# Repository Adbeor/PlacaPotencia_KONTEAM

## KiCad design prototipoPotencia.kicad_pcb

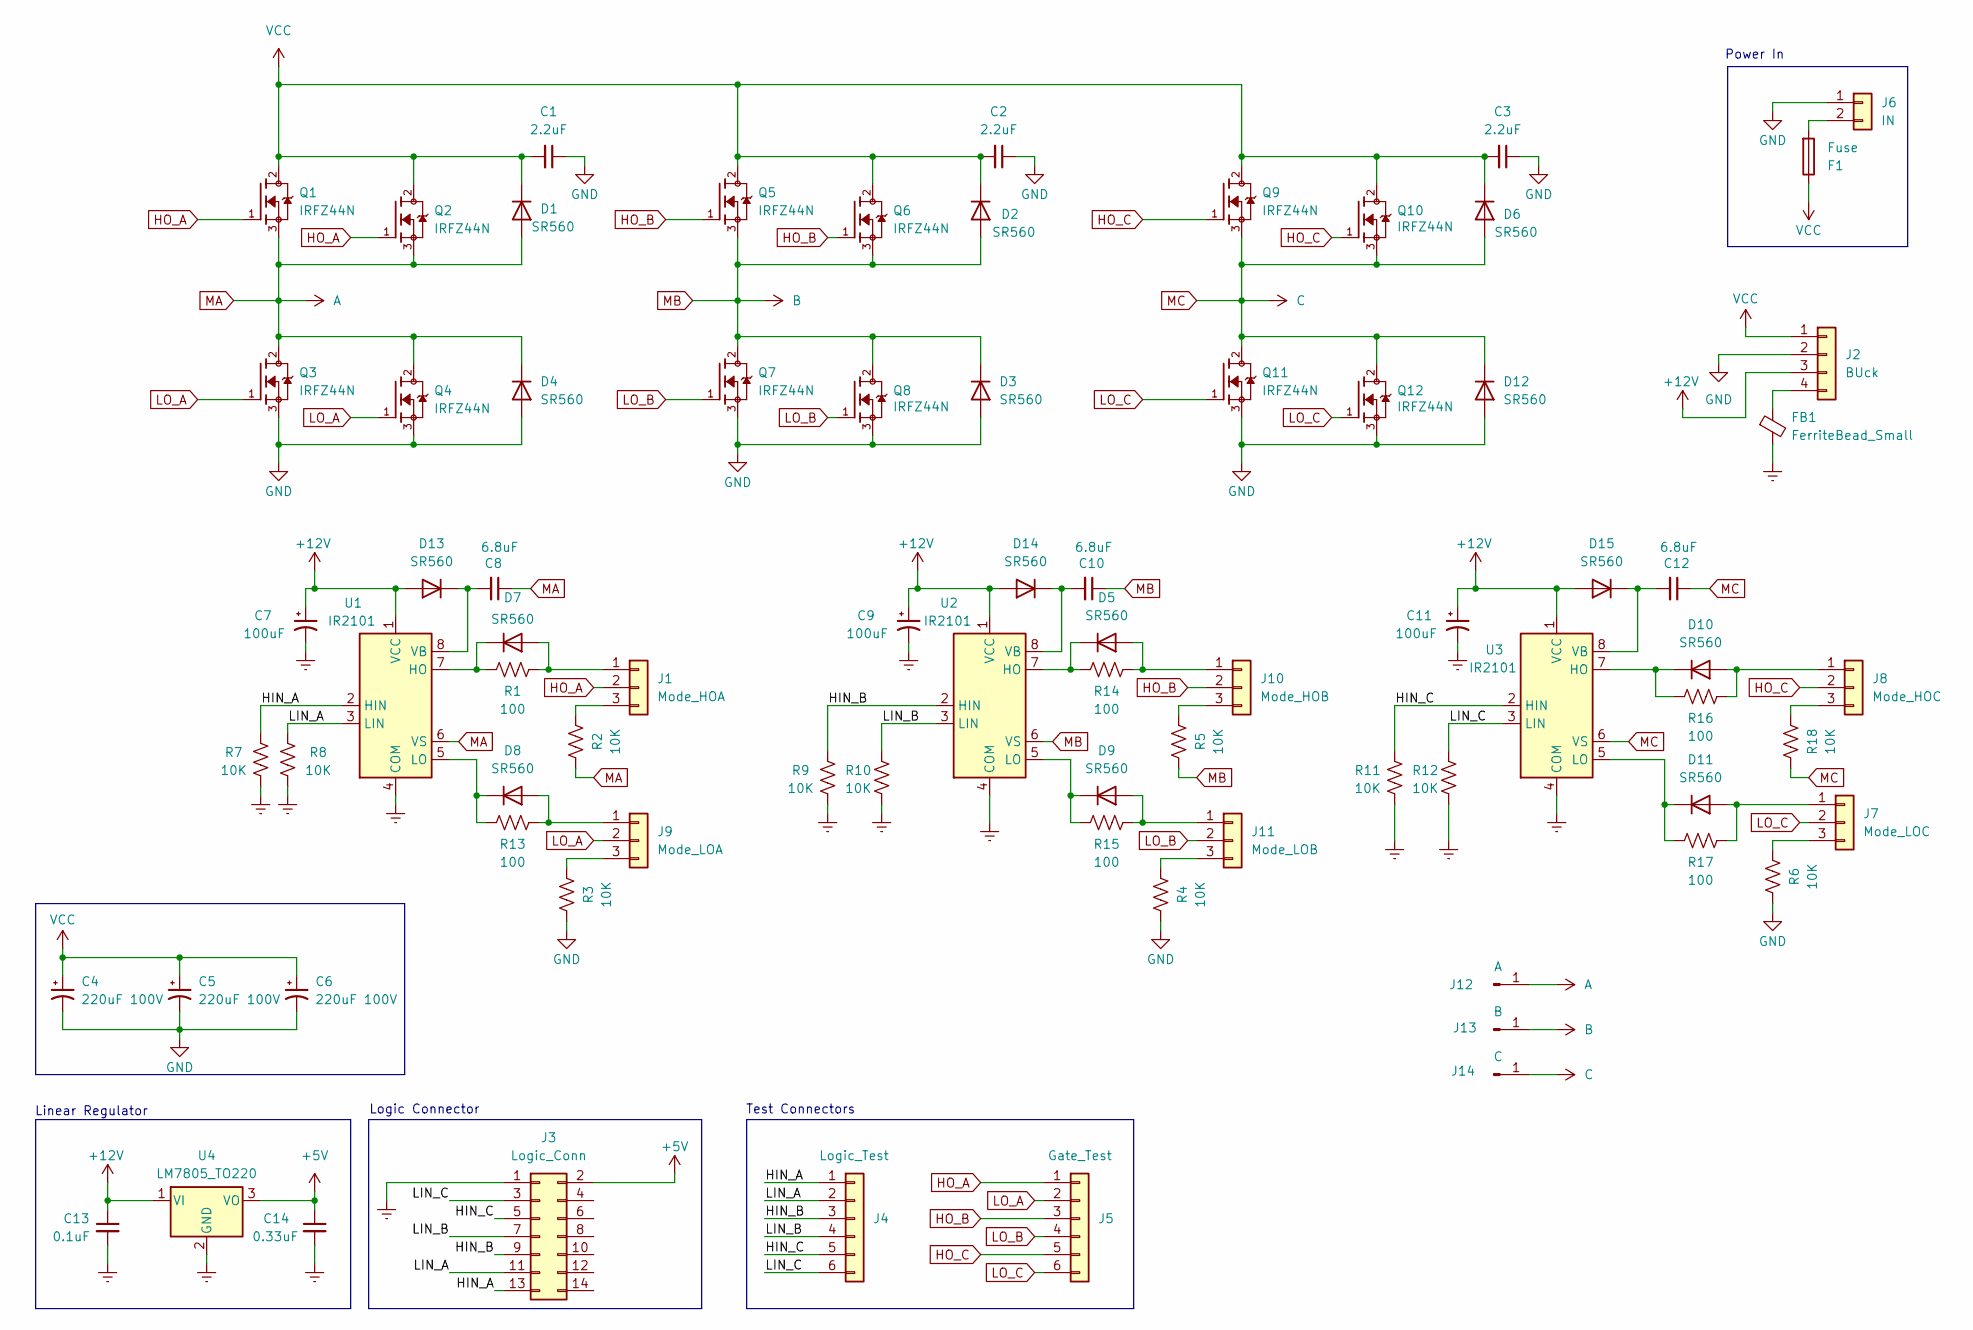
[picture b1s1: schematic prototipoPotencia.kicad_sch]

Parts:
C1, C2, C3: 2.2uF; C_Disc_D5.0mm_W2.5mm_P2.50mm
C4, C5, C6: 220uF 100V; CP_Radial_D10.0mm_P2.50mm
C7, C9, C11: 100uF; C_Radial_D6.3mm_H11.0mm_P2.50mm
C8, C10, C12: 6.8uF; CP_Radial_Tantal_D4.5mm_P2.50mm
C13: 0.1uF; C_Disc_D7.5mm_W2.5mm_P5.00mm
C14: 0.33uF; C_Disc_D7.5mm_W2.5mm_P5.00mm
D1, D2, D3, D4, D5, D6, D7, D8, D9, D10, D11, D12, D13, D14, D15: SR560; D_DO-35_SOD27_P7.62mm_Horizontal
F1: Fuse; Fuse_Littelfuse-LVR100
FB1: FerriteBead_Small; R_Axial_DIN0204_L3.6mm_D1.6mm_P7.62mm_Horizontal
J1: Mode_HOA; PinHeader_1x03_P2.54mm_Vertical
J2: BUck; DC_DC_LM2596_small
J3: Logic_Conn; IDC-Header_2x07_P2.54mm_Vertical
J4: Logic_Test; PinSocket_1x06_P2.54mm_Vertical
J5: Gate_Test; PinSocket_1x06_P2.54mm_Vertical
J6: IN; AMASS_XT60-F_1x02_P7.20mm_Vertical
J7: Mode_LOC; PinHeader_1x03_P2.54mm_Vertical
J8: Mode_HOC; PinHeader_1x03_P2.54mm_Vertical
J9: Mode_LOA; PinHeader_1x03_P2.54mm_Vertical
J10: Mode_HOB; PinHeader_1x03_P2.54mm_Vertical
J11: Mode_LOB; PinHeader_1x03_P2.54mm_Vertical
J12: A; TestPoint_Loop_D3.80mm_Drill2.0mm
J13: B; TestPoint_Loop_D3.80mm_Drill2.0mm
J14: C; TestPoint_Loop_D3.80mm_Drill2.0mm
Q1, Q2, Q3, Q4, Q5, Q6, Q7, Q8, Q9, Q10, Q11, Q12: IRFZ44N; TO254P1016X419X2286-3; PARTREV 09/21/10
R1, R13, R14, R15, R16, R17: 100; R_Axial_DIN0204_L3.6mm_D1.6mm_P7.62mm_Horizontal
R2, R3, R4, R5, R6, R7, R8, R9, R10, R11, R12, R18: 10K; R_Axial_DIN0204_L3.6mm_D1.6mm_P7.62mm_Horizontal
U1, U2, U3: IR2101; DIP-8_W7.62mm_LongPads
U4: LM7805_TO220; TO-220-3_Vertical

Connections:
+5V: C14.1, J3.2, U4.3 (VO)
+12V: C7.1, C9.1, C11.1, C13.1, D13.2 (A), D14.2 (A), D15.2 (A), J2.3, U1.1 (VCC), U2.1 (VCC), U3.1 (VCC), U4.1 (VI)
/HIN_A: J3.13, J4.1, R7.1, U1.2 (HIN)
/HIN_B: J3.9, J4.3, R9.1, U2.2 (HIN)
/HIN_C: J3.5, J4.5, R11.1, U3.2 (HIN)
/LIN_A: J3.11, J4.2, R8.1, U1.3 (LIN)
/LIN_B: J3.7, J4.4, R10.1, U2.3 (LIN)
/LIN_C: J3.3, J4.6, R12.1, U3.3 (LIN)
Earth: C7.2, C9.2, C11.2, C13.2, C14.2, FB1.2, J3.1, R7.2, R8.2, R9.2, R10.2, R11.2, R12.2, U1.4 (COM), U2.4 (COM), U3.4 (COM), U4.2 (GND)
GND: C1.1, C2.1, C3.1, C4.2, C5.2, C6.2, D3.2 (A), D4.2 (A), D12.2 (A), J2.2, J6.1, Q3.3, Q4.3, Q7.3, Q8.3, Q11.3, Q12.3, R3.2, R4.2, R6.2
HO_A: J1.2, J5.1, Q1.1, Q2.1
HO_B: J5.3, J10.2, Q5.1, Q6.1
HO_C: J5.5, J8.2, Q9.1, Q10.1
LO_A: J5.2, J9.2, Q3.1, Q4.1
LO_B: J5.4, J11.2, Q7.1, Q8.1
LO_C: J5.6, J7.2, Q11.1, Q12.1
MA: C8.1, D1.2 (A), D4.1 (K), J12.1, Q1.3, Q2.3, Q3.2, Q4.2, R2.2, U1.6 (VS)
MB: C10.1, D2.2 (A), D3.1 (K), J13.1, Q5.3, Q6.3, Q7.2, Q8.2, R5.2, U2.6 (VS)
MC: C12.1, D6.2 (A), D12.1 (K), J14.1, Q9.3, Q10.3, Q11.2, Q12.2, R18.2, U3.6 (VS)
unnamed: D5.2 (A), J10.1, R14.1
unnamed: D5.1 (K), R14.2, U2.7 (HO)
unnamed: D7.2 (A), J1.1, R1.1
unnamed: D7.1 (K), R1.2, U1.7 (HO)
unnamed: D8.2 (A), J9.1, R13.1
unnamed: D8.1 (K), R13.2, U1.5 (LO)
unnamed: D9.2 (A), J11.1, R15.1
unnamed: D9.1 (K), R15.2, U2.5 (LO)
unnamed: D10.2 (A), J8.1, R16.1
unnamed: D10.1 (K), R16.2, U3.7 (HO)
unnamed: D11.2 (A), J7.1, R17.1
unnamed: D11.1 (K), R17.2, U3.5 (LO)
unnamed: C8.2, D13.1 (K), U1.8 (VB)
unnamed: C10.2, D14.1 (K), U2.8 (VB)
unnamed: C12.2, D15.1 (K), U3.8 (VB)
unnamed: J1.3, R2.1
unnamed: FB1.1, J2.4
unnamed: F1.2, J6.2
unnamed: J7.3, R6.1
unnamed: J8.3, R18.1
unnamed: J9.3, R3.1
unnamed: J10.3, R5.1
unnamed: J11.3, R4.1
VCC: C1.2, C2.2, C3.2, C4.1, C5.1, C6.1, D1.1 (K), D2.1 (K), D6.1 (K), F1.1, J2.1, Q1.2, Q2.2, Q5.2, Q6.2, Q9.2, Q10.2

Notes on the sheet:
Linear Regulator
Logic Connector
Power In
Test Connectors

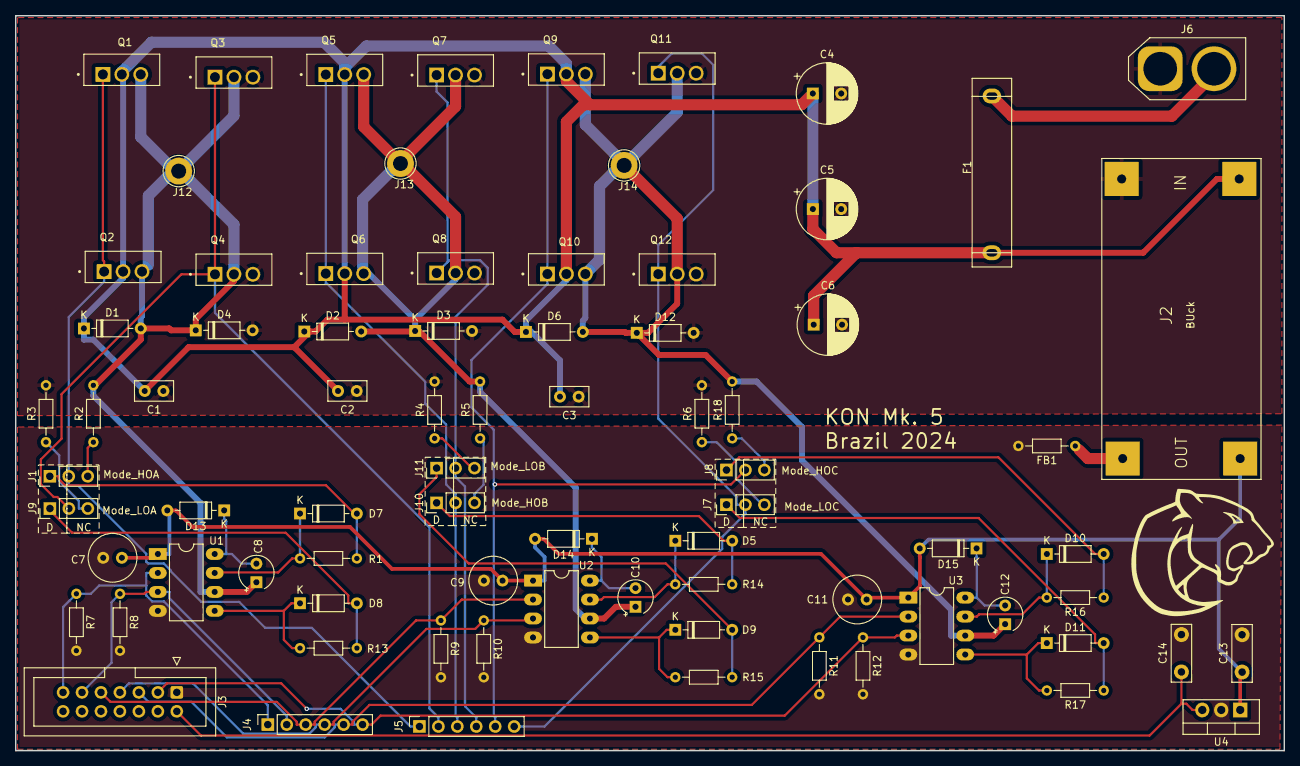
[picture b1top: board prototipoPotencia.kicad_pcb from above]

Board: 2 copper layers, 170.0 x 98.5 mm, 79 parts (0 on the bottom side), 43 nets.

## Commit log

2024-08-11 Inicial
